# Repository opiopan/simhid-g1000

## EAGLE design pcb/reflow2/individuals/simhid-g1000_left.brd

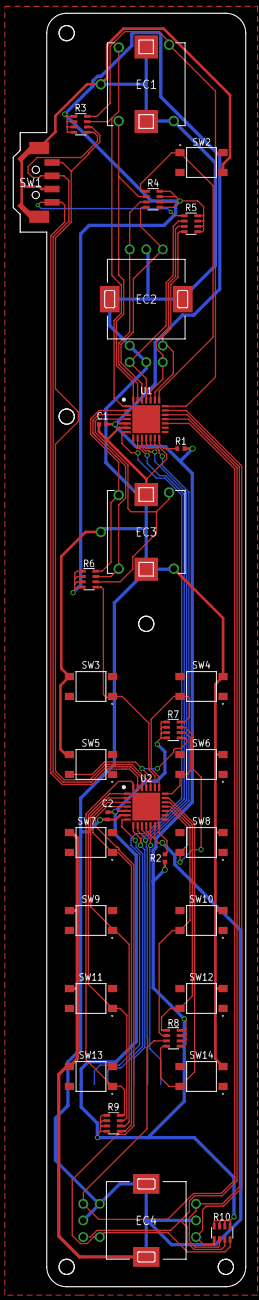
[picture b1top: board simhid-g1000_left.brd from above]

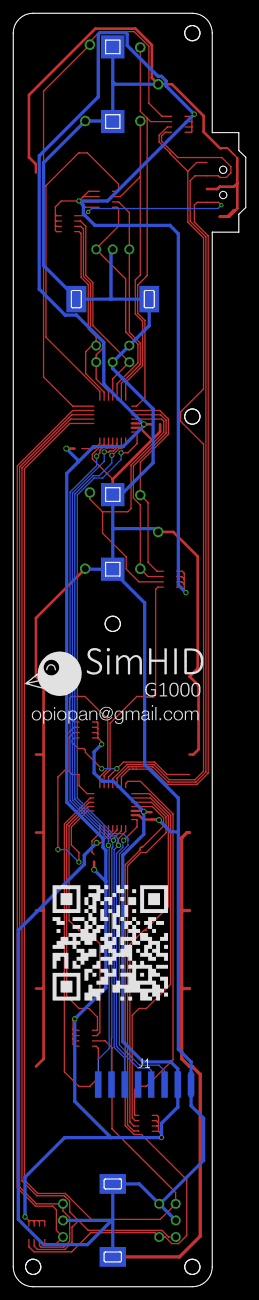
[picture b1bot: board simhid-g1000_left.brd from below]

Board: 2 copper layers, 35.0 x 192.0 mm, 35 parts (3 on the bottom side), 41 nets.

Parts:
C1, C2: 0.1uF; RCL_C0402_HS
EC1, EC3: EC12D1524403
EC2, EC4: EC11EBB24C03
J1: PCB-INTERCONNECT
R1, R2: 10KΩ; RCL_R0402_HS
R3, R4, R5, R6, R7, R8, R9, R10: 10KΩ x 4; BCN164A_1
SW1: SLLB510100-HS
SW2, SW3, SW4, SW5, SW6, SW7, SW8, SW9, SW10, SW11, SW12, SW13, SW14: TS-1109S-B-B
U1, U2: MCP23S17-E; QFN65P600X600X100-29N
U$1: SHIMHID-G1000-QRCODE
U$2: SIMHID-G1000-LOGO

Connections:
+3V3: C1.1, C2.1, J1.2, R1.2, R2.2, R3.5, R3.6, R3.7, R3.8, R4.5, R4.6, R4.7, R4.8, R5.5, R5.6, R5.7, R5.8, R6.5, R6.6, R6.7, R6.8, R7.5, R7.6, R7.7, R7.8, R8.5, R8.6, R8.7, R8.8, R9.5, R9.6, R9.7, R9.8, R10.5, R10.6, R10.7, R10.8, U1.5, U2.5
AUX_1: R5.1, SW1.1, U2.27
AUX_2: R3.2, SW1.2, U2.25
AUX_T: R3.1, SW1.T, U2.26
BTN1: R4.1, SW2.1, U1.22
BTN2: R6.1, SW3.1, U2.23
BTN3: R7.4, SW4.2, U2.22
BTN4: R7.1, SW5.2, U2.24
BTN5: R7.2, SW6.2, U2.21
BTN6: R9.1, SW7.1, U2.3
BTN7: R7.3, SW8.2, U2.17
BTN8: R9.2, SW9.1, U2.2
BTN9: R8.2, SW10.2, U2.18
BTN10: R9.3, SW11.1, U2.1
BTN11: R8.1, SW12.2, U2.19
BTN12: R9.4, SW13.1, U2.28
BTN13: R8.4, SW14.2, U2.20
EC1_PUSH: EC1.D, R3.4, U1.21
EC2_PUSH: EC2.D, R5.4, U1.23
EC3_PUSH: EC3.D, R6.2, U1.4
EC4_PUSH: EC4.D, R10.4, U2.4
EXT1_CS: J1.3, U1.7
EXT2_CS: J1.4, U2.7
GND: C1.2, C2.2, EC1.C, EC1.E, EC1.MH1, EC1.MH2, EC1.MH3, EC1.MH4, EC2.C1, EC2.C2, EC2.E, EC2.NH1, EC2.NH2, EC2.NH3, EC2.NH4, EC3.C, EC3.E, EC3.MH1, EC3.MH2, EC3.MH3, EC3.MH4, EC4.C1, EC4.C2, EC4.E, EC4.NH1, EC4.NH2, EC4.NH3, EC4.NH4, J1.1, SW1.C, SW1.MH1, SW1.MH2, SW1.MH3, SW1.MH4, SW2.4, SW3.4, SW4.3, SW5.4, SW6.3, SW7.4, SW8.3, SW9.4, SW10.3, SW11.4, SW12.3, SW13.4, SW14.3, U1.6, U1.11, U1.12, U1.13, U2.6, U2.11, U2.12, U2.13
MISO: J1.8, U1.10, U2.10
MOSI: J1.7, U1.9, U2.9
unnamed: R1.1, U1.14
unnamed: R2.1, U2.14
RE1A: EC1.A, R4.2, U1.28
RE1B: EC1.B, R3.3, U1.1
RE2A: EC2.A1, R4.4, U1.26
RE2B: EC2.B1, R4.3, U1.27
RE3A: EC2.A2, R5.3, U1.24
RE3B: EC2.B2, R5.2, U1.25
RE4A: EC3.A, R6.3, U1.3
RE4B: EC3.B, R6.4, U1.2
RE5A: EC4.A1, R10.1, U1.20
RE5B: EC4.B1, R10.2, U1.19
RE6A: EC4.A2, R10.3, U1.18
RE6B: EC4.B2, R8.3, U1.17
SCLK: J1.6, U1.8, U2.8

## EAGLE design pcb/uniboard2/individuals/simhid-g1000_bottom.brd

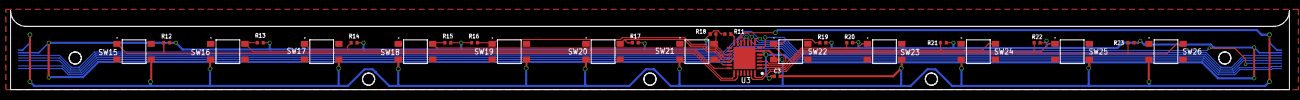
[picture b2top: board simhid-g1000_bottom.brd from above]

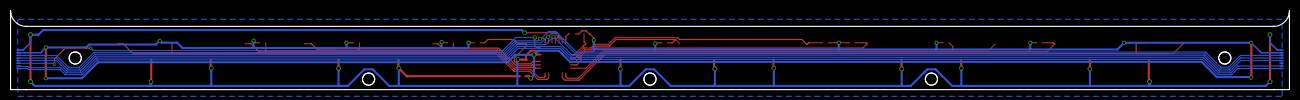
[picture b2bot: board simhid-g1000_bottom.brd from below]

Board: 2 copper layers, 242.5 x 15.0 mm, 29 parts (2 on the bottom side), 21 nets.

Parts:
C3: 0.1uF; RCL_C0402_HS
J2: PCB-INTERCONNECT-LB; PCB-INTERCONNECT-L
J3: PCB-INTERCONNECT-RB; PCB-INTERCONNECT-R
R11: 10KΩ; RCL_R0402_HS
R12, R13, R14, R15, R16, R17, R18, R19, R20, R21, R22, R23: RCL_R0402_HS
SW15, SW16, SW17, SW18, SW19, SW20, SW21, SW22, SW23, SW24, SW25, SW26: TS-1109S-B-B
U3: MCP23S17-E; QFN65P600X600X100-29N

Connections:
+3V3: C3.1, J2.2, J3.2, R11.2, R12.2, R13.2, R14.2, R15.2, R16.2, R17.2, R18.2, R19.2, R20.2, R21.2, R22.2, R23.2, U3.5
EXT1_CS: J2.8, J3.8
EXT2_CS: J2.7, J3.7
EXT3_CS: J3.6, U3.7
GND: C3.2, J2.1, J3.1, SW15.4, SW16.3, SW17.4, SW18.3, SW19.4, SW20.3, SW21.3, SW22.3, SW23.4, SW24.3, SW25.4, SW26.3, U3.6, U3.11, U3.12, U3.13
MISO: J2.5, J3.5, U3.10
MOSI: J2.4, J3.4, U3.9
RESET: R11.1, U3.14
SCLK: J2.3, J3.3, U3.8
SW15: R12.1, SW15.1, U3.23
SW16: R13.1, SW16.2, U3.22
SW17: R14.1, SW17.1, U3.21
SW18: R15.1, SW18.2, U3.20
SW19: R16.1, SW19.1, U3.18
SW20: R17.1, SW20.2, U3.19
SW21: R18.1, SW21.2, U3.17
SW22: R19.1, SW22.1, U3.3
SW23: R20.1, SW23.1, U3.2
SW24: R21.1, SW24.2, U3.1
SW25: R22.1, SW25.1, U3.28
SW26: R23.1, SW26.2, U3.27
